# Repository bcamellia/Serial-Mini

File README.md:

Not actively developing, still wish to revisit at some point.

Serial Mini is an original rework of my PS/2 mini keyboard to further reduce input latency. It sends keystrokes using RS232 at up to a 115k baud rate. The keystrokes are processed and registered by a Linux kernel driver. The driver first converts a TTY line into a serial port object, connects the serial keyboard, and registers keystrokes using an interrupt. Using this method, I could achieve a round-trip latency of up to ~0.5ms.

Features:
* Bootloader support (in-development)
* Integrated MAX232 (in-development)
* Hardware based switch debouncing
* RBG Backlighting with controls (in-development)

To-do:
* Remove unused libraries
* Double check connections
* Add measurements and example video
* Write firmware without using CCS

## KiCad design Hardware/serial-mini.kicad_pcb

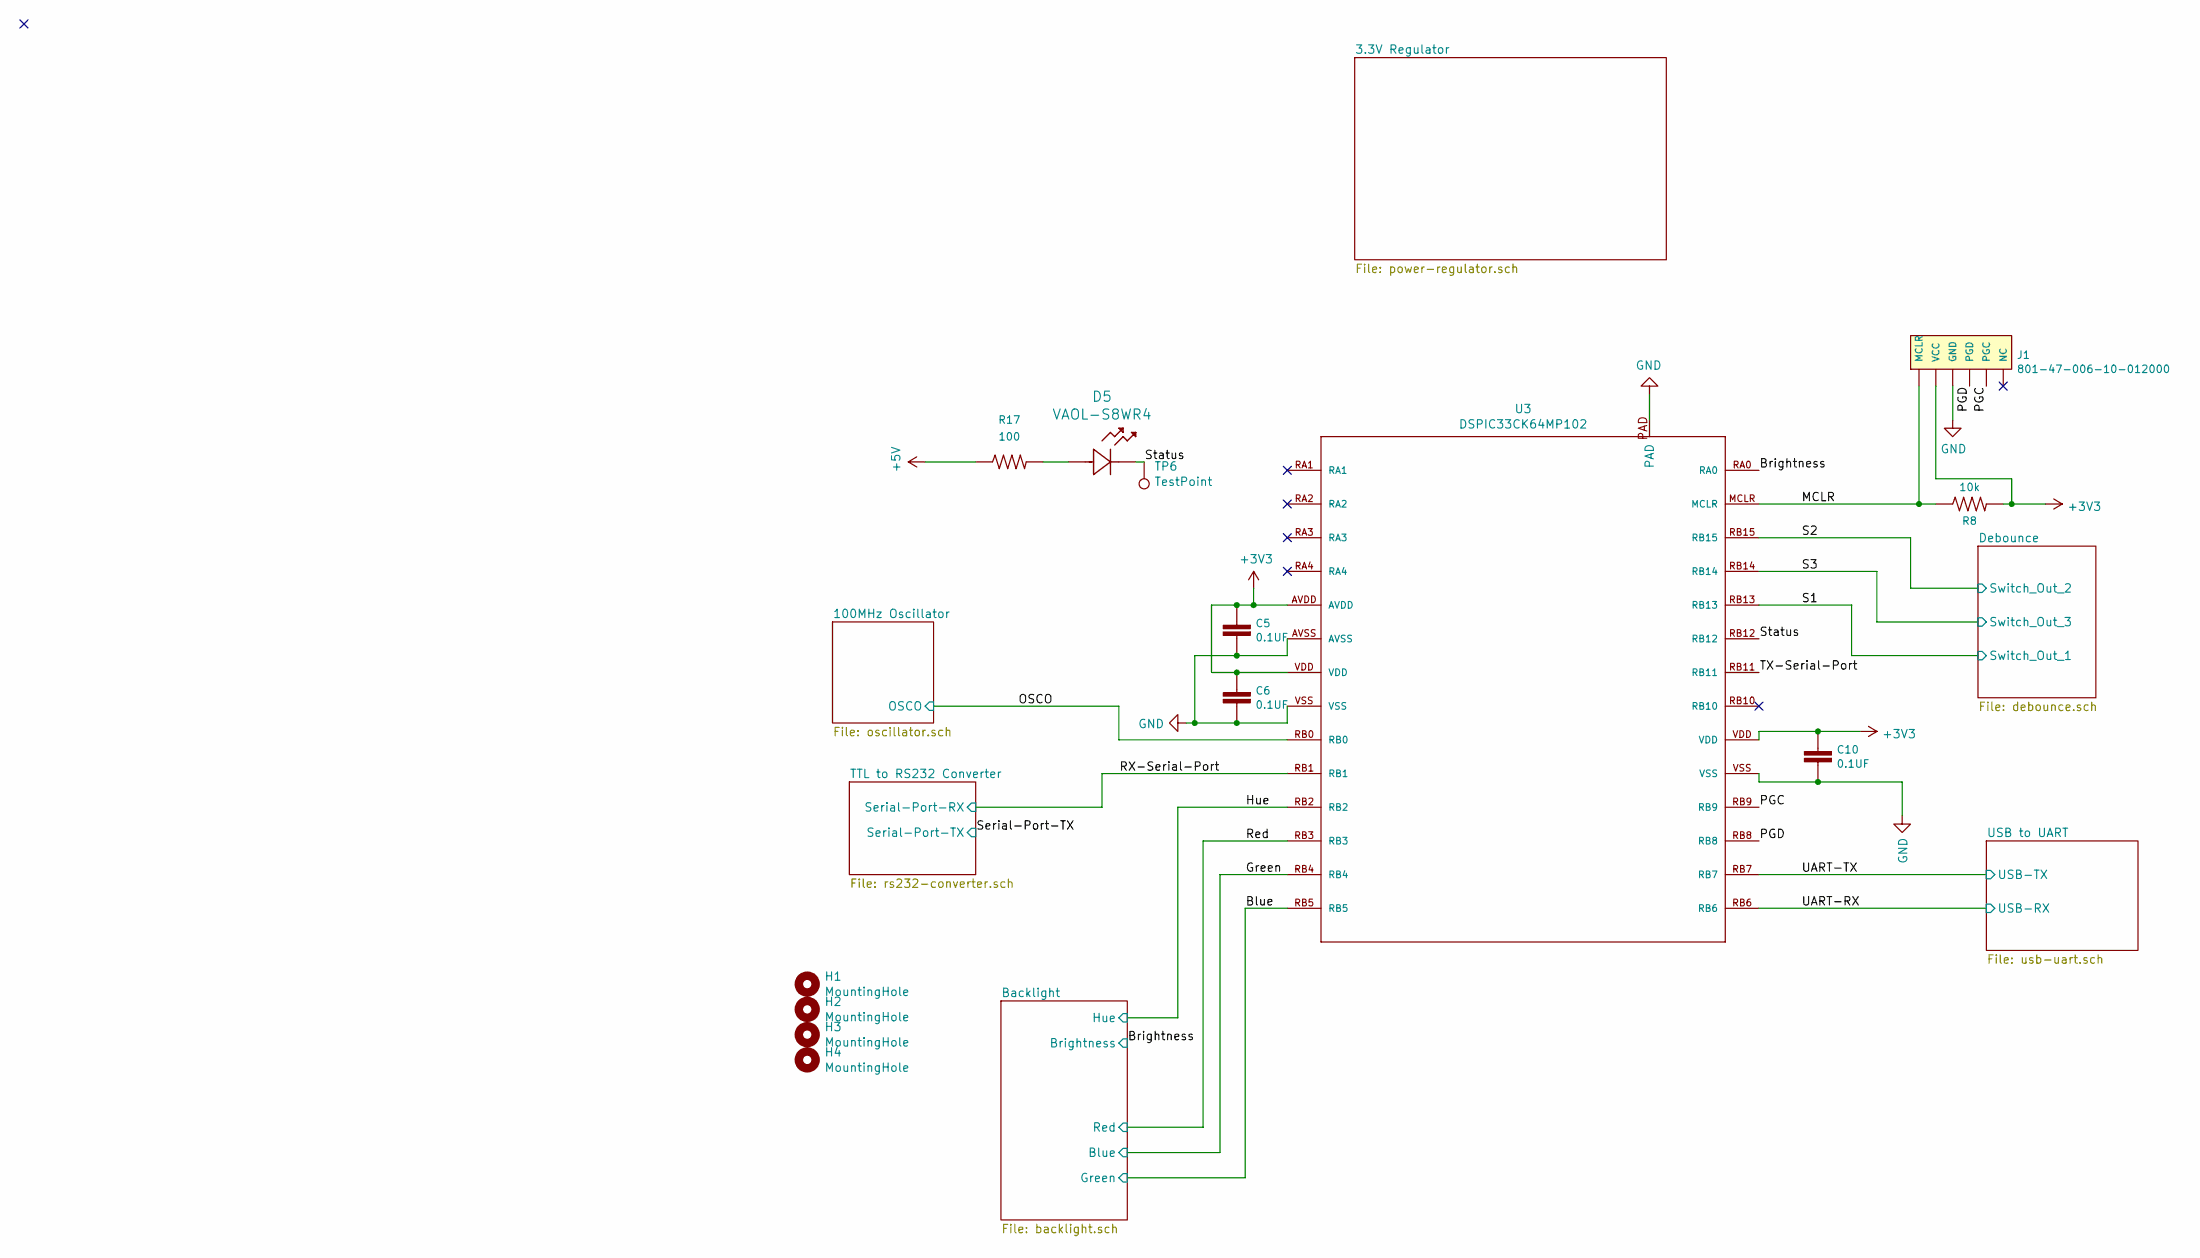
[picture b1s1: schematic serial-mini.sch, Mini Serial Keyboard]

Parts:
C5, C6, C10: 0.1UF; C_0603_1608Metric_Pad1.05x0.95mm_HandSolder
D5: VAOL-S8WR4
H1, H2, H3, H4: MountingHole; MountingHole_2.5mm_Pad_Via
J1: 801-47-006-10-012000; PICKITv3
R8: 10k; R_0603_1608Metric_Pad1.05x0.95mm_HandSolder
R17: 100; R_0603_1608Metric_Pad1.05x0.95mm_HandSolder
TP6: TestPoint; TestPoint_Pad_1.0x1.0mm
U3: DSPIC33CK64MP102; ‎DSPIC33CK32MP102

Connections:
+3V3: C5.2, C6.2, C10.2, J1.VCC, R8.2, U3.AVDD, U3.VDD; also elsewhere on the board
+5V: R17.1; also elsewhere on the board
/Blue: U3.RB5; also elsewhere on the board
/Brightness: U3.RA0; also elsewhere on the board
/Green: U3.RB4; also elsewhere on the board
/Hue: U3.RB2; also elsewhere on the board
/MCLR: J1.MCLR, R8.1, U3.MCLR
/OSCO: U3.RB0; also elsewhere on the board
/PGC: J1.PGC, U3.RB9
/PGD: J1.PGD, U3.RB8
/RX-Serial-Port: U3.RB1; also elsewhere on the board
/Red: U3.RB3; also elsewhere on the board
/S1: U3.RB13; also elsewhere on the board
/S2: U3.RB15; also elsewhere on the board
/S3: U3.RB14; also elsewhere on the board
/Status: D5.1, TP6.1, U3.RB12
/TX-Serial-Port: U3.RB11
/UART-RX: U3.RB6; also elsewhere on the board
/UART-TX: U3.RB7; also elsewhere on the board
GND: C5.1, C6.1, C10.1, J1.GND, U3.AVSS, U3.PAD, U3.VSS; also elsewhere on the board
unnamed: D5.2, R17.2

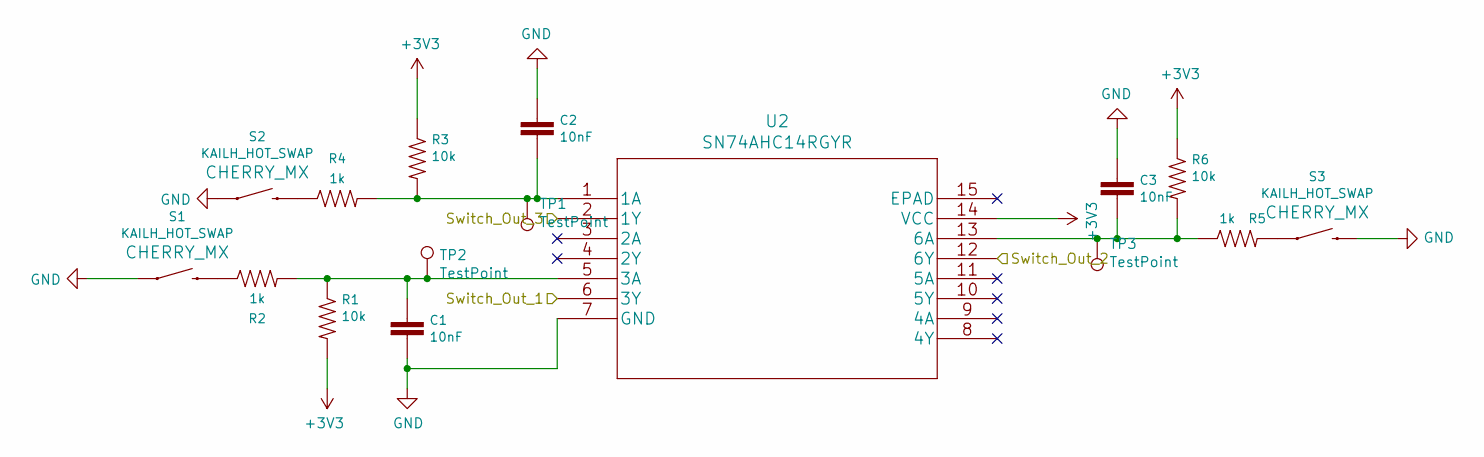
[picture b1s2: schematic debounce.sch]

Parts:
C1, C2, C3: 10nF; C_0603_1608Metric_Pad1.05x0.95mm_HandSolder
R1, R3, R6: 10k; R_0603_1608Metric_Pad1.05x0.95mm_HandSolder
R2, R4, R5: 1k; R_0603_1608Metric_Pad1.05x0.95mm_HandSolder
S1, S2, S3: KAILH_HOT_SWAP; Kailh_MX_Socket
TP1, TP2, TP3: TestPoint; TestPoint_Pad_1.0x1.0mm
U2: SN74AHC14RGYR

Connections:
+3V3: R1.2, R3.1, R6.1, U2.14 (VCC); also elsewhere on the board
/S1: U2.6 (3Y); also elsewhere on the board
/S2: U2.12 (6Y); also elsewhere on the board
/S3: U2.2 (1Y); also elsewhere on the board
GND: C1.2, C2.1, C3.1, S1.1, S2.1, S3.2, U2.7 (GND); also elsewhere on the board
unnamed: C1.1, R1.1, R2.2, TP2.1, U2.5 (3A)
unnamed: C2.2, R3.2, R4.2, TP1.1, U2.1 (1A)
unnamed: C3.2, R5.1, R6.2, TP3.1, U2.13 (6A)
unnamed: R2.1, S1.2
unnamed: R4.1, S2.2
unnamed: R5.2, S3.1

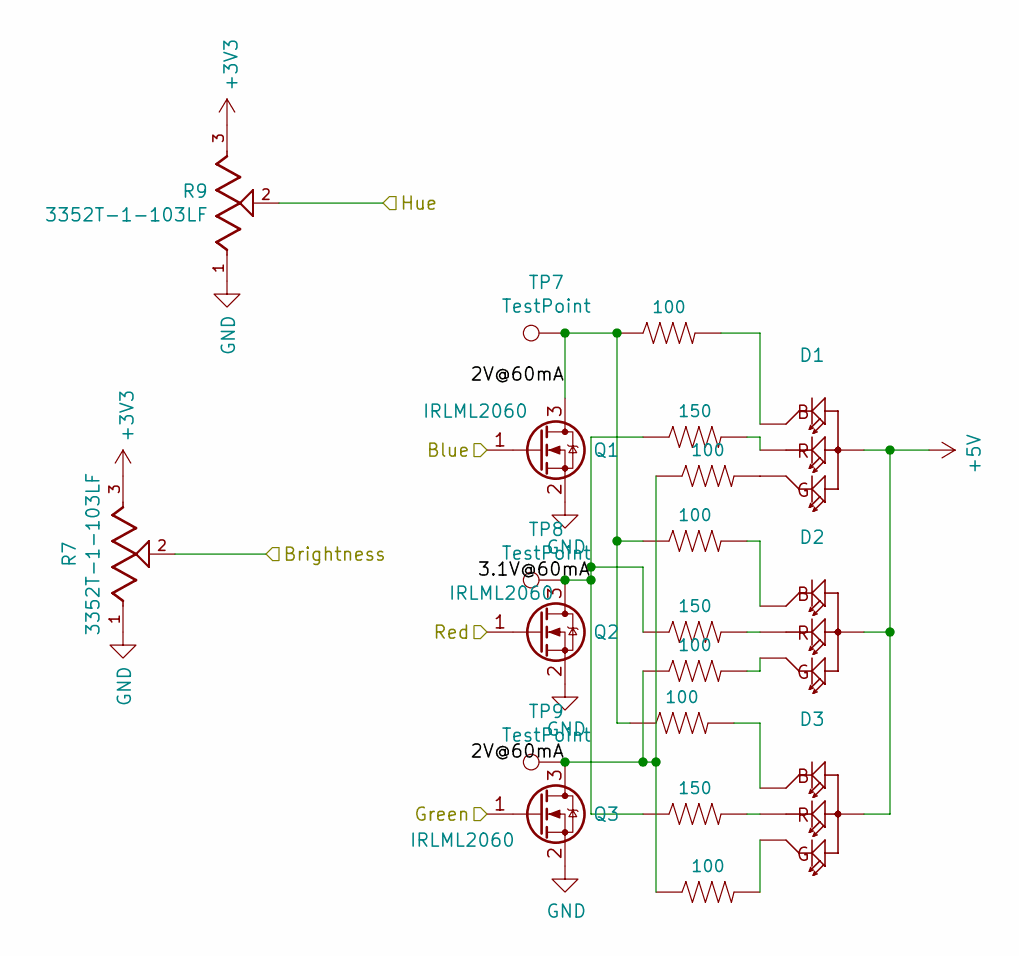
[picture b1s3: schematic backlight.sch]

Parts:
D1, D2, D3: CLVBA-FKA; SOL150P350X210-4N
Q1, Q2, Q3: IRLML2060; IRLML2060TRPBF
R7, R9: 3352T-1-103LF; TRIM_3352T-1-103LF
R10, R11, R13, R15, R18, R19: 100; R_0603_1608Metric_Pad1.05x0.95mm_HandSolder
R12, R14, R16: 150; R_0603_1608Metric_Pad1.05x0.95mm_HandSolder
TP7, TP8, TP9: TestPoint; TestPoint_Pad_1.0x1.0mm

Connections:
+3V3: R7.3, R9.3; also elsewhere on the board
+5V: D1.2, D2.2, D3.2; also elsewhere on the board
/Backlight/2V@60mA: Q1.3 (D), Q3.3 (D), R10.1, R11.1, R13.1, R15.1, R18.1, R19.1, TP7.1, TP9.1
/Backlight/3.1V@60mA: Q2.3 (D), R12.1, R14.1, R16.1, TP8.1
/Blue: Q3.1 (G); also elsewhere on the board
/Brightness: R7.2; also elsewhere on the board
/Green: Q1.1 (G); also elsewhere on the board
/Hue: R9.2; also elsewhere on the board
/Red: Q2.1 (G); also elsewhere on the board
GND: Q1.2 (S), Q2.2 (S), Q3.2 (S), R7.1, R9.1; also elsewhere on the board
unnamed: D1.1, R12.2
unnamed: D1.3, R10.2
unnamed: D1.4, R18.2
unnamed: D2.1, R14.2
unnamed: D2.3, R13.2
unnamed: D2.4, R15.2
unnamed: D3.1, R16.2
unnamed: D3.3, R11.2
unnamed: D3.4, R19.2

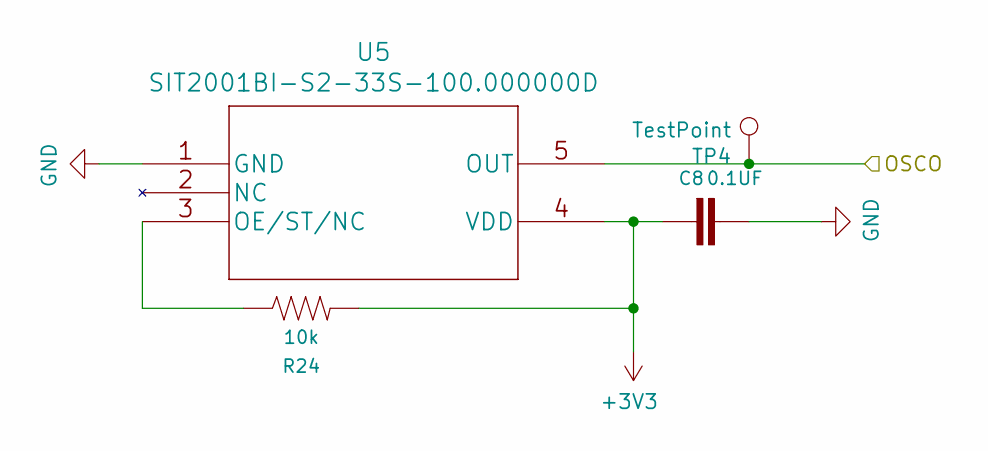
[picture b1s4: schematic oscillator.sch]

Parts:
C8: 0.1UF; C_0603_1608Metric_Pad1.05x0.95mm_HandSolder
R24: 10k; R_0603_1608Metric_Pad1.05x0.95mm_HandSolder
TP4: TestPoint; TestPoint_Pad_1.0x1.0mm
U5: SIT2001BI-S2-33S-100.000000D

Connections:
+3V3: C8.2, R24.2, U5.4 (VDD); also elsewhere on the board
/OSCO: TP4.1, U5.5 (OUT); also elsewhere on the board
GND: C8.1, U5.1 (GND); also elsewhere on the board
unnamed: R24.1, U5.3 (OE/ST/NC)

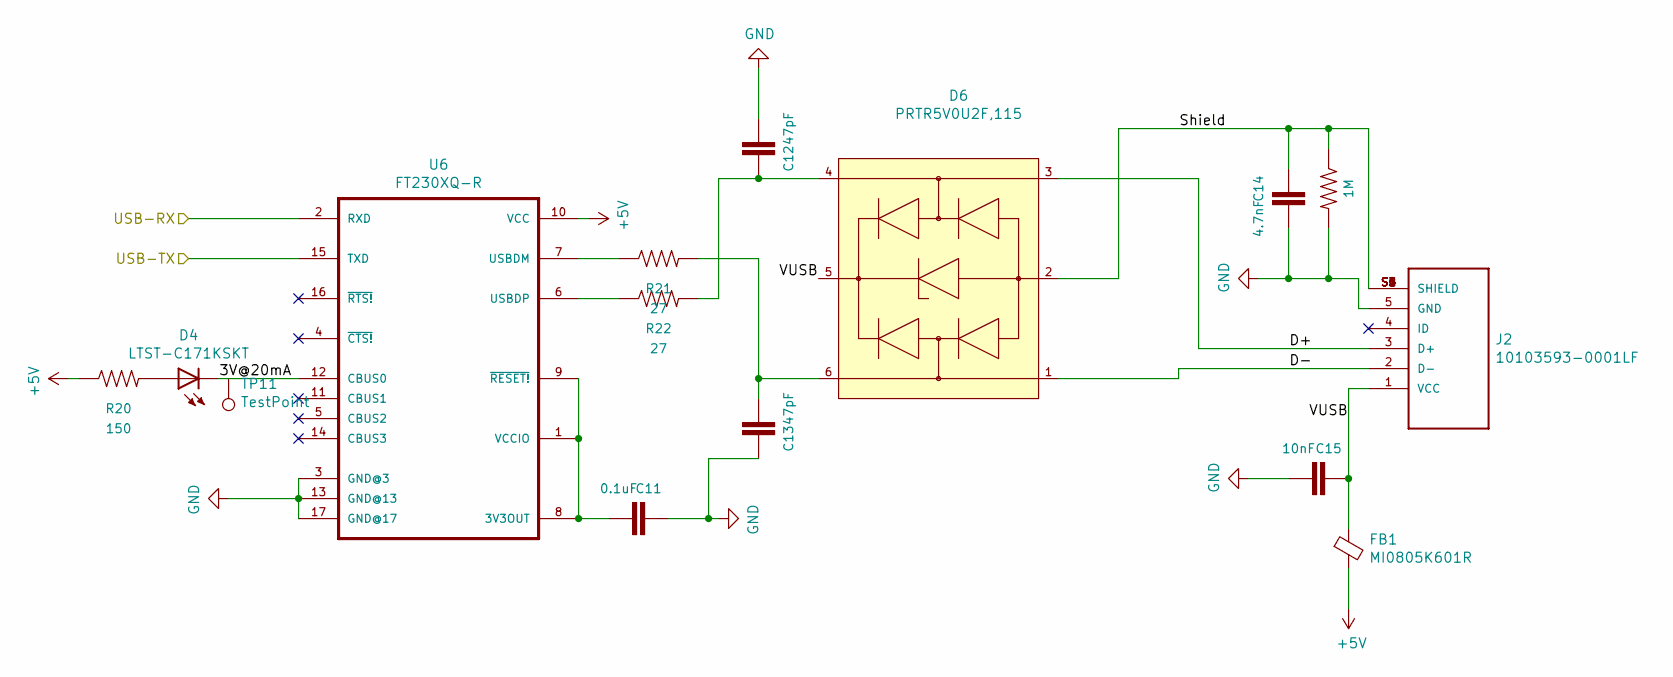
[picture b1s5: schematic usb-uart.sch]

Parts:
C11: 0.1uF; C_0603_1608Metric_Pad1.05x0.95mm_HandSolder
C12, C13: 47pF; C_0603_1608Metric_Pad1.05x0.95mm_HandSolder
C14: 4.7nF; C_0603_1608Metric_Pad1.05x0.95mm_HandSolder
C15: 10nF; C_0603_1608Metric_Pad1.05x0.95mm_HandSolder
D4: LTST-C171KSKT; DIOC200X125X110
D6: PRTR5V0U2F,115; Nexperia-SOT886-11_2018-0-MFG; breakdown voltage 6V; mouser part number 771-PRTR5V0U2F-T/R; digikey description TVS DIODE 5.5V 6XSON SOT886
FB1: MI0805K601R; R_0805_2012Metric_Pad1.15x1.40mm_HandSolder
J2: 10103593-0001LF; AMPHENOL_10103593-0001LF
R20: 150; R_0603_1608Metric_Pad1.05x0.95mm_HandSolder
R21, R22: 27; R_0603_1608Metric_Pad1.05x0.95mm_HandSolder
R23: 1M; R_0603_1608Metric_Pad1.05x0.95mm_HandSolder
TP11: TestPoint; TestPoint_Pad_1.0x1.0mm
U6: FT230XQ-R; FT230XQ

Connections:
+5V: FB1.2, R20.1, U6.10 (VCC); also elsewhere on the board
/UART-RX: U6.2 (RXD); also elsewhere on the board
/UART-TX: U6.15 (TXD); also elsewhere on the board
/USB to UART/3V@20mA: D4.-, TP11.1, U6.12 (CBUS0)
/USB to UART/D+: D6.3 (I/O2), J2.3 (D+)
/USB to UART/D-: D6.1 (I/O1), J2.2 (D-)
/USB to UART/Shield: C14.2, D6.2 (GND), J2.S1 (SHIELD), J2.S2 (SHIELD), J2.S3 (SHIELD), J2.S4 (SHIELD), J2.S5 (SHIELD), J2.S6 (SHIELD), R23.1
/USB to UART/VUSB: C15.2, D6.5 (VCC), FB1.1, J2.1 (VCC)
GND: C11.2, C12.1, C13.2, C14.1, C15.1, J2.5 (GND), R23.2, U6.3 (GND@3), U6.13 (GND@13), U6.17 (GND@17); also elsewhere on the board
unnamed: C11.1, U6.1 (VCCIO), U6.8 (3V3OUT), U6.9 (~RESET!~)
unnamed: C12.2, D6.4 (I/O2), R22.2
unnamed: C13.1, D6.6 (I/O1), R21.2
unnamed: D4.+, R20.2
unnamed: R21.1, U6.7 (USBDM)
unnamed: R22.1, U6.6 (USBDP)

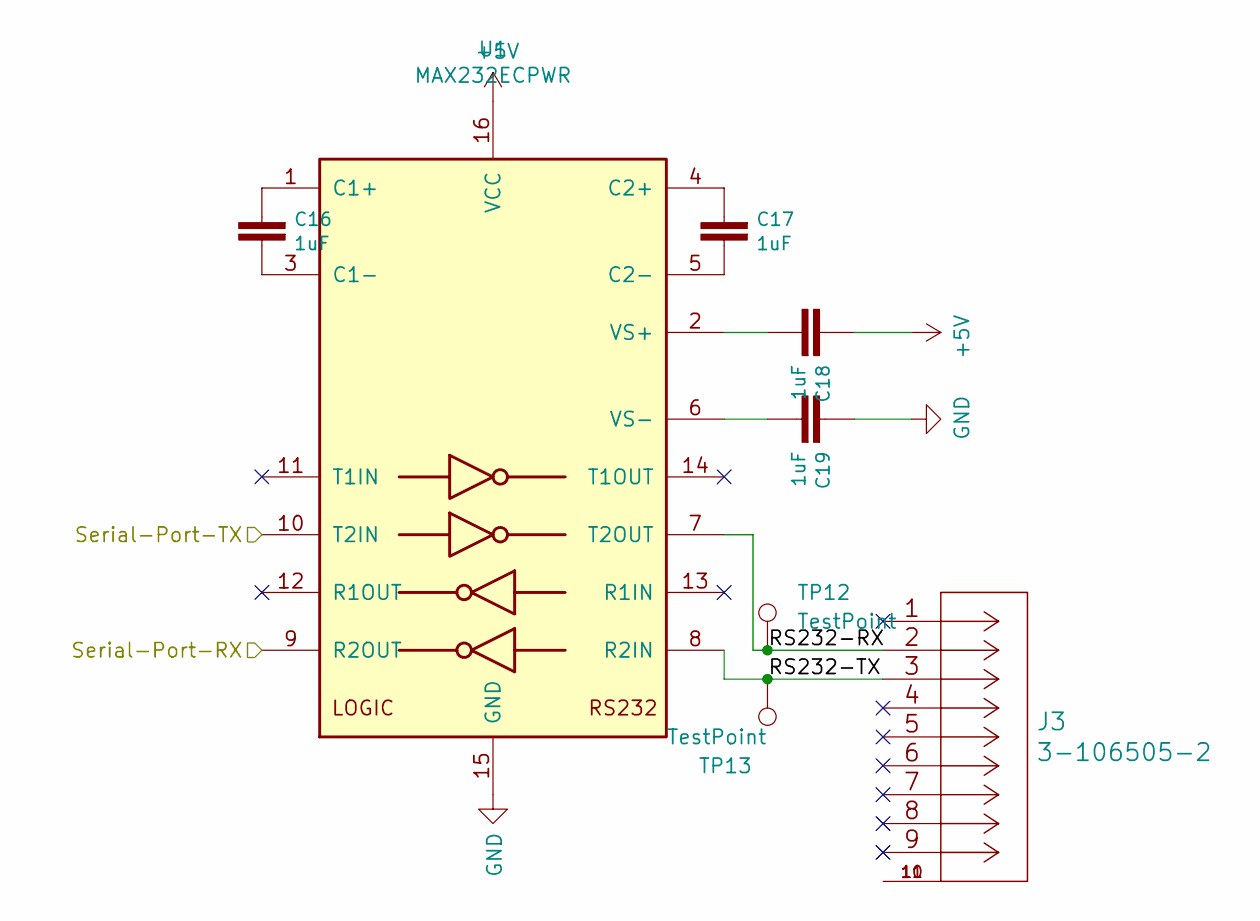
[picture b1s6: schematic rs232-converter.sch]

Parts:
C16, C17, C18, C19: 1uF; C_0603_1608Metric_Pad1.05x0.95mm_HandSolder
J3: 3-106505-2
TP12, TP13: TestPoint; TestPoint_Pad_1.0x1.0mm
U1: MAX232ECPWR

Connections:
+5V: C18.2, U1.16 (VCC); also elsewhere on the board
/RX-Serial-Port: U1.9 (R2OUT); also elsewhere on the board
/Serial-Port-TX: U1.10 (T2IN)
/TTL to RS232 Converter/RS232-RX: J3.2, TP12.1, U1.7 (T2OUT)
/TTL to RS232 Converter/RS232-TX: J3.3, TP13.1, U1.8 (R2IN)
GND: C19.2, U1.15 (GND); also elsewhere on the board
unnamed: C16.1, U1.3 (C1-)
unnamed: C16.2, U1.1 (C1+)
unnamed: C17.1, U1.5 (C2-)
unnamed: C17.2, U1.4 (C2+)
unnamed: C18.1, U1.2 (VS+)
unnamed: C19.1, U1.6 (VS-)
unnamed: J3.10, J3.11

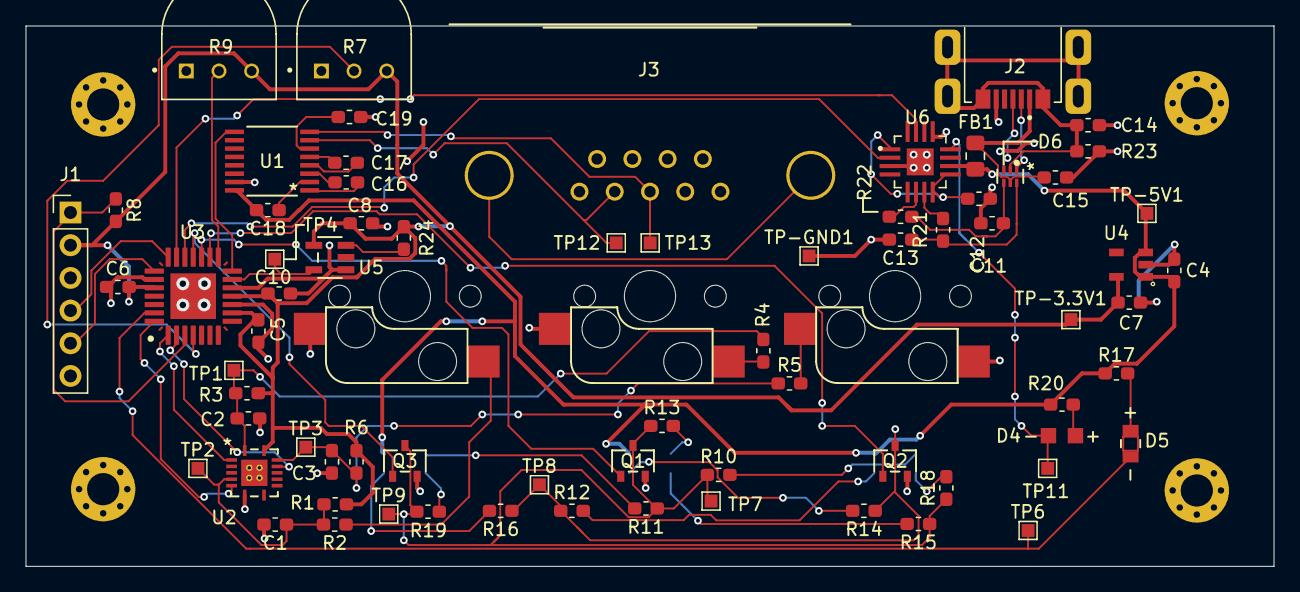
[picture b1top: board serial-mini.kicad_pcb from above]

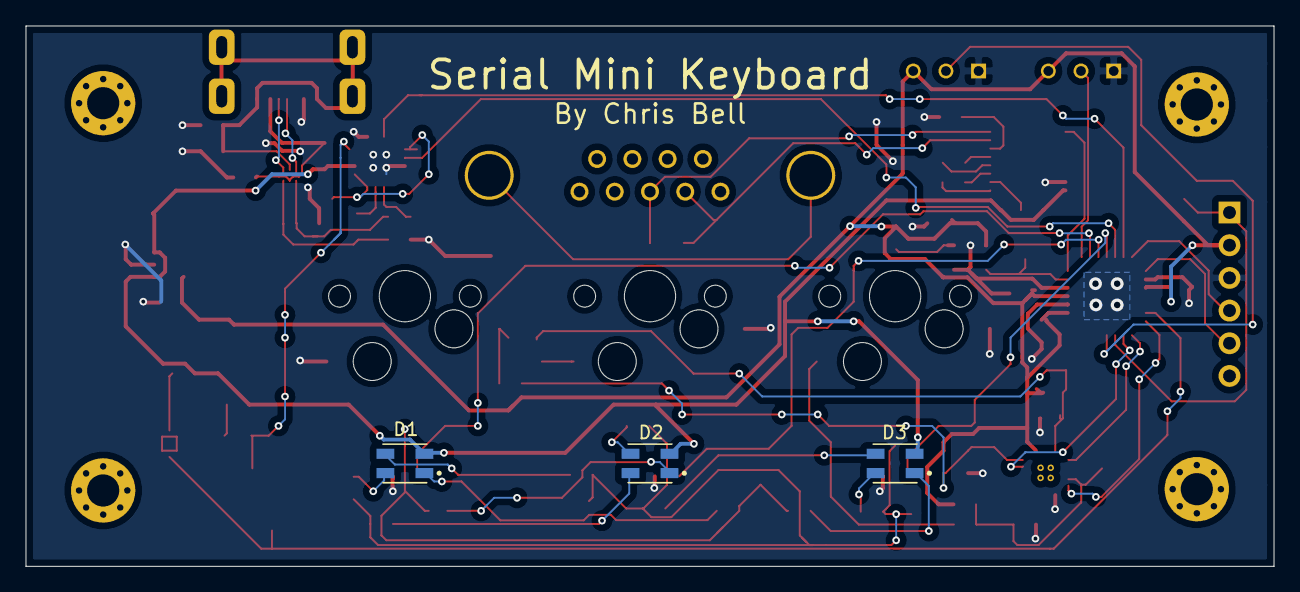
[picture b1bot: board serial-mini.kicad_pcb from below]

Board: 4 copper layers, 97.0 x 42.0 mm, 82 parts (3 on the bottom side), 58 nets.

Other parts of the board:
C4, C7: 1UF; C_0603_1608Metric_Pad1.05x0.95mm_HandSolder
TP-3.3V1, TP-5V1: TestPoint; TestPoint_Pad_1.0x1.0mm
TP-GND1: TestPoint; TestPoint_Pad_1.0x1.0mm
U4: MIC5504-3.3YM5-TR; MIC5504

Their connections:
+3V3: C7.1, TP-3.3V1.1, U4.5; also elsewhere on the board
+5V: C4.1, TP-5V1.1, U4.1, U4.3; also elsewhere on the board
GND: C4.2, C7.2, TP-GND1.1, U4.2; also elsewhere on the board

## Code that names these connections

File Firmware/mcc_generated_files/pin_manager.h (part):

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*/
/**
  @Summary
    Sets the GPIO pin, RB1, high using LATB1.

  @Description
    Sets the GPIO pin, RB1, high using LATB1.

  @Preconditions
    The RB1 must be set to an output.
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#define IO_RB1_SetHigh()          (_LATB1 = 1)
/**
  @Summary
    Sets the GPIO pin, RB1, low using LATB1.

  @Description
    Sets the GPIO pin, RB1, low using LATB1.

  @Preconditions
    The RB1 must be set to an output.
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#define IO_RB1_SetLow()           (_LATB1 = 0)
/**
  @Summary
    Toggles the GPIO pin, RB1, using LATB1.

  @Description
    Toggles the GPIO pin, RB1, using LATB1.

  @Preconditions
    The RB1 must be set to an output.
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#define IO_RB1_Toggle()           (_LATB1 ^= 1)
/**
  @Summary
    Reads the value of the GPIO pin, RB1.

  @Description
    Reads the value of the GPIO pin, RB1.

  @Preconditions
    None.
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    </code>

*/
#define IO_RB1_GetValue()         _RB1
/**
  @Summary
    Configures the GPIO pin, RB1, as an input.

  @Description
    Configures the GPIO pin, RB1, as an input.

  @Preconditions
    None.
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#define IO_RB1_SetDigitalInput()  (_TRISB1 = 1)
/**
  @Summary
    Configures the GPIO pin, RB1, as an output.

  @Description
    Configures the GPIO pin, RB1, as an output.

  @Preconditions
    None.
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#define IO_RB11_SetDigitalOutput() (_TRISB11 = 0)
/**
  @Summary
    Sets the GPIO pin, RB12, high using LATB12.

  @Description
    Sets the GPIO pin, RB12, high using LATB12.

  @Preconditions
    The RB12 must be set to an output.
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#define Status_SetHigh()          (_LATB12 = 1)
/**
  @Summary
    Sets the GPIO pin, RB12, low using LATB12.

  @Description
    Sets the GPIO pin, RB12, low using LATB12.

  @Preconditions
    The RB12 must be set to an output.
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#define Status_SetLow()           (_LATB12 = 0)
/**
  @Summary
    Toggles the GPIO pin, RB12, using LATB12.

  @Description
    Toggles the GPIO pin, RB12, using LATB12.

  @Preconditions
    The RB12 must be set to an output.
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#define Status_Toggle()           (_LATB12 ^= 1)
/**
  @Summary
    Reads the value of the GPIO pin, RB12.

  @Description
    Reads the value of the GPIO pin, RB12.

  @Preconditions
    None.
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    </code>

*/
#define Status_GetValue()         _RB12
/**
  @Summary
    Configures the GPIO pin, RB12, as an input.

  @Description
    Configures the GPIO pin, RB12, as an input.

  @Preconditions
    None.
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#define Status_SetDigitalInput()  (_TRISB12 = 1)
/**
  @Summary
    Configures the GPIO pin, RB12, as an output.

  @Description
    Configures the GPIO pin, RB12, as an output.

  @Preconditions
    None.
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#define Status_SetDigitalOutput() (_TRISB12 = 0)
/**
  @Summary
    Sets the GPIO pin, RB13, high using LATB13.

  @Description
    Sets the GPIO pin, RB13, high using LATB13.

  @Preconditions
    The RB13 must be set to an output.
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#define IO_RB13_SetHigh()          (_LATB13 = 1)
/**
  @Summary
    Sets the GPIO pin, RB13, low using LATB13.

  @Description
    Sets the GPIO pin, RB13, low using LATB13.

  @Preconditions
    The RB13 must be set to an output.
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#define IO_RB13_SetLow()           (_LATB13 = 0)
/**
  @Summary
    Toggles the GPIO pin, RB13, using LATB13.

  @Description
    Toggles the GPIO pin, RB13, using LATB13.

  @Preconditions
    The RB13 must be set to an output.
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#define IO_RB13_Toggle()           (_LATB13 ^= 1)
/**
  @Summary
    Reads the value of the GPIO pin, RB13.

  @Description
    Reads the value of the GPIO pin, RB13.

  @Preconditions
    None.
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    </code>

*/
#define IO_RB13_GetValue()         _RB13
/**
  @Summary
    Configures the GPIO pin, RB13, as an input.

  @Description
    Configures the GPIO pin, RB13, as an input.

  @Preconditions
    None.
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#define IO_RB13_SetDigitalInput()  (_TRISB13 = 1)
/**
  @Summary
    Configures the GPIO pin, RB13, as an output.

  @Description
    Configures the GPIO pin, RB13, as an output.

  @Preconditions
    None.
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#define IO_RB13_SetDigitalOutput() (_TRISB13 = 0)
/**
  @Summary
    Sets the GPIO pin, RB14, high using LATB14.

  @Description
    Sets the GPIO pin, RB14, high using LATB14.

  @Preconditions
    The RB14 must be set to an output.
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#define IO_RB14_SetHigh()          (_LATB14 = 1)
/**
  @Summary
    Sets the GPIO pin, RB14, low using LATB14.

  @Description
    Sets the GPIO pin, RB14, low using LATB14.

  @Preconditions
    The RB14 must be set to an output.
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#define IO_RB14_SetLow()           (_LATB14 = 0)
/**
  @Summary
    Toggles the GPIO pin, RB14, using LATB14.

  @Description
    Toggles the GPIO pin, RB14, using LATB14.

  @Preconditions
    The RB14 must be set to an output.
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#define IO_RB14_Toggle()           (_LATB14 ^= 1)
/**
  @Summary
    Reads the value of the GPIO pin, RB14.

  @Description
    Reads the value of the GPIO pin, RB14.

  @Preconditions
    None.
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    </code>

*/
#define IO_RB14_GetValue()         _RB14
/**
  @Summary
    Configures the GPIO pin, RB14, as an input.

  @Description
    Configures the GPIO pin, RB14, as an input.

  @Preconditions
    None.
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#define IO_RB14_SetDigitalInput()  (_TRISB14 = 1)
/**
  @Summary
    Configures the GPIO pin, RB14, as an output.

  @Description
    Configures the GPIO pin, RB14, as an output.

  @Preconditions
    None.
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#define IO_RB14_SetDigitalOutput() (_TRISB14 = 0)
/**
  @Summary
    Sets the GPIO pin, RB15, high using LATB15.

  @Description
    Sets the GPIO pin, RB15, high using LATB15.

  @Preconditions
    The RB15 must be set to an output.
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#define IO_RB15_SetHigh()          (_LATB15 = 1)
/**
  @Summary
    Sets the GPIO pin, RB15, low using LATB15.

  @Description
    Sets the GPIO pin, RB15, low using LATB15.

  @Preconditions
    The RB15 must be set to an output.
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#define IO_RB15_SetLow()           (_LATB15 = 0)
/**
  @Summary
    Toggles the GPIO pin, RB15, using LATB15.

  @Description
    Toggles the GPIO pin, RB15, using LATB15.

  @Preconditions
    The RB15 must be set to an output.
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#define IO_RB15_Toggle()           (_LATB15 ^= 1)
/**
  @Summary
    Reads the value of the GPIO pin, RB15.

  @Description
    Reads the value of the GPIO pin, RB15.

  @Preconditions
    None.
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    </code>

*/
#define IO_RB15_GetValue()         _RB15
/**
  @Summary
    Configures the GPIO pin, RB15, as an input.

  @Description
    Configures the GPIO pin, RB15, as an input.

  @Preconditions
    None.
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#define IO_RB15_SetDigitalInput()  (_TRISB15 = 1)
/**
  @Summary
    Configures the GPIO pin, RB15, as an output.

  @Description
    Configures the GPIO pin, RB15, as an output.

  @Preconditions
    None.
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#define IO_RB15_SetDigitalOutput() (_TRISB15 = 0)
/**
  @Summary
    Sets the GPIO pin, RB2, high using LATB2.

  @Description
    Sets the GPIO pin, RB2, high using LATB2.

  @Preconditions
    The RB2 must be set to an output.
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#define IO_RB2_SetHigh()          (_LATB2 = 1)
/**
  @Summary
    Sets the GPIO pin, RB2, low using LATB2.

  @Description
    Sets the GPIO pin, RB2, low using LATB2.

  @Preconditions
    The RB2 must be set to an output.
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#define IO_RB2_SetLow()           (_LATB2 = 0)
/**
  @Summary
    Toggles the GPIO pin, RB2, using LATB2.

  @Description
    Toggles the GPIO pin, RB2, using LATB2.

  @Preconditions
    The RB2 must be set to an output.
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#define IO_RB2_Toggle()           (_LATB2 ^= 1)
/**
  @Summary
    Reads the value of the GPIO pin, RB2.

  @Description
    Reads the value of the GPIO pin, RB2.

  @Preconditions
    None.
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    </code>

*/
#define IO_RB2_GetValue()         _RB2
/**
  @Summary
    Configures the GPIO pin, RB2, as an input.

  @Description
    Configures the GPIO pin, RB2, as an input.

  @Preconditions
    None.
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#define IO_RB2_SetDigitalInput()  (_TRISB2 = 1)
/**
  @Summary
    Configures the GPIO pin, RB2, as an output.

  @Description
    Configures the GPIO pin, RB2, as an output.

  @Preconditions
    None.
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#define IO_RB2_SetDigitalOutput() (_TRISB2 = 0)
/**
  @Summary
    Sets the GPIO pin, RB3, high using LATB3.

  @Description
    Sets the GPIO pin, RB3, high using LATB3.

  @Preconditions
    The RB3 must be set to an output.
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#define IO_RB3_SetHigh()          (_LATB3 = 1)
/**
  @Summary
    Sets the GPIO pin, RB3, low using LATB3.

  @Description
    Sets the GPIO pin, RB3, low using LATB3.

  @Preconditions
    The RB3 must be set to an output.
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#define IO_RB3_SetLow()           (_LATB3 = 0)
/**
  @Summary
    Toggles the GPIO pin, RB3, using LATB3.

  @Description
    Toggles the GPIO pin, RB3, using LATB3.

  @Preconditions
    The RB3 must be set to an output.
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#define IO_RB3_Toggle()           (_LATB3 ^= 1)
/**
  @Summary
    Reads the value of the GPIO pin, RB3.

  @Description
    Reads the value of the GPIO pin, RB3.

  @Preconditions
    None.
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    </code>

*/
#define IO_RB3_GetValue()         _RB3
/**
  @Summary
    Configures the GPIO pin, RB3, as an input.

  @Description
    Configures the GPIO pin, RB3, as an input.

  @Preconditions
    None.
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#define IO_RB3_SetDigitalInput()  (_TRISB3 = 1)
/**
  @Summary
    Configures the GPIO pin, RB3, as an output.

  @Description
    Configures the GPIO pin, RB3, as an output.

  @Preconditions
    None.
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
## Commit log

2020-06-19 Add driver and firmware files
2020-07-05 Update main.c
    Code formatting
2020-07-15 Start working on new schematic
    Cleaning up unused library symbols, adding symbols to single library
2020-07-15 Add RGB Leds
    Simplified design to 3 keys and added potentiometers
2020-07-17 Update schematic symbols
    Started adding schematic symbols to project specific library, mapping footprints to symbols
2020-07-20 Update symbols/footprints
    Linked most symbols to their datasheets, updated more footprint/symbol footprints.
    Also added status indicator LED
2020-07-20 Semantic changes
2020-07-20 Move design folder
2020-07-20 Add more labels
    Swapped some LEDs
2020-07-20 Add test points
    Swapped RGB LEDs, updated pin types to pass ERC, removed unused libraries/footprints
2020-07-20 Remove unused footprint references
2020-07-20 Update PCB
2020-07-26 Try optimizing PCB layout
2020-07-26 Initial placement of footprints
2020-07-26 Begin routing
2020-07-26 Continue routing
2020-07-26 Finish routing
2020-07-26 Add missing courtyards
2020-07-27 Add EMI/ESD protection on USB port
2020-07-27 Use hierarchical sheets
    Added MAX232 also
2020-07-28 Complete new schematic
    Added MAX232 and fixed test points on switches
2020-07-28 Add more net labels
    Begin redesigning PCB again
2020-07-28 Add missing power regulator .sch
2020-08-02 Complete initial routing
2020-08-02 Fix incorrect footprints
    Fixed incorrect footprint for IRLML2060 and updated LED values to use CLVBA-FKA.
    Also started deleting unneccessary test points
2020-08-02 Fix DRC errors
    Courtyard overlaps
2020-08-02 Adjust all track/text widths
2020-08-02 Finish placing footprint labels
2020-08-02 Fix faulty debounce circuit
    Used wrong value resistor/misplaced on each switch.
    Also adjusted value of RC circuits for a time constant of 1 microsecond (was 1 millisecond before)
2020-08-02 Fix weird routing
2020-08-02 Add 3D file references
    Generated first build
2020-08-03 Fix USB through holes
    Cleaned-up unused files
2020-08-03 Add BOM
2020-08-11 Fix PRTR5V0U2F footprint
    Footprint was flipped wrong way on PCB, also removed BOM folder since it messed up Linguist
2020-08-12 Add new firmware project
2020-11-27 Make leadless package pads longer, add vias
2020-12-02 Adjust formatting

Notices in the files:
Firmware/mcc_generated_files/pin_manager.h:
(c) 2020 Microchip Technology Inc. and its subsidiaries. You may use this
parts and their libraries:
Copyright 2016 Accelerated Designs. All rights reserved.
